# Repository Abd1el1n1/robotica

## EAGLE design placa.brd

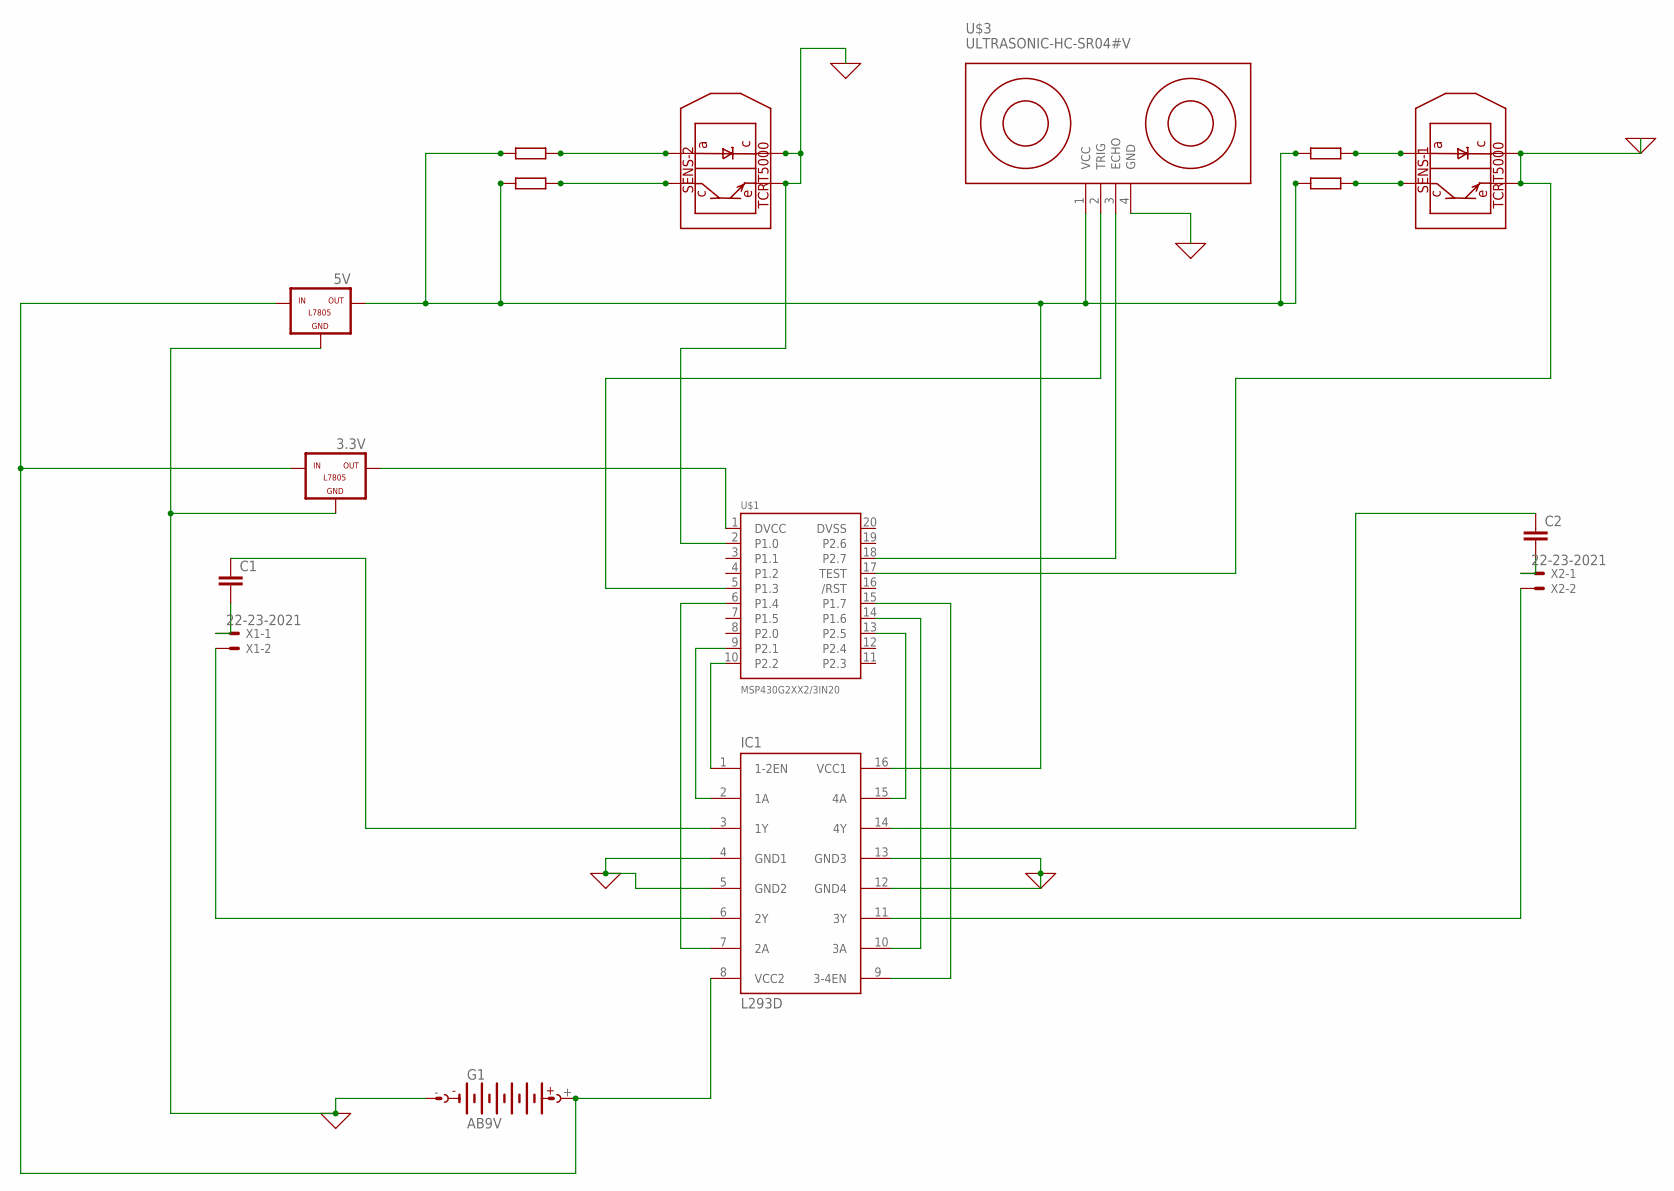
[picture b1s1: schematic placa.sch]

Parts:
3.3V, 5V: -L7805; L7805
C1, C2: C2.5/2; C2.5-2
G1: AB9V
IC1: L293D; DIL16
SENS-1, SENS-2: TCRT5000; 5000
U$1: MSP430G2XX2/3IN20; DIL20
U$3: ULTRASONIC-HC-SR04#V
X1, X2: 22-23-2021

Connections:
0: 3.3V.GND, 5V.GND, G1.-, IC1.4 (GND1), IC1.5 (GND2), IC1.12 (GND4), IC1.13 (GND3), SENS-1.P$2, SENS-1.P$4, SENS-2.P$2, SENS-2.P$4, U$1.2 (P1.0), U$1.17 (TEST), U$3.4 (GND)
DVSS: U$1.20 (DVSS)
unnamed: 3.3V.OUT, U$1.1 (DVCC)
unnamed: IC1.1 (1-2EN), U$1.10 (P2.2)
unnamed: IC1.2 (1A), U$1.9 (P2.1)
unnamed: IC1.7 (2A), U$1.6 (P1.4)
unnamed: C1.1, IC1.3 (1Y)
unnamed: C1.2, X1.1
unnamed: IC1.15 (4A), U$1.13 (P2.5)
unnamed: IC1.10 (3A), U$1.14 (P1.6)
unnamed: IC1.9 (3-4EN), U$1.15 (P1.7)
unnamed: IC1.11 (3Y), X2.2
unnamed: IC1.6 (2Y), X1.2
unnamed: C2.2, X2.1
unnamed: C2.1, IC1.14 (4Y)
unnamed: 5V.OUT, IC1.16 (VCC1), U$3.1 (VCC)
unnamed: 3.3V.IN, 5V.IN, G1.+, IC1.8 (VCC2)
unnamed: U$1.5 (P1.3), U$3.2 (TRIG)
unnamed: U$1.18 (P2.7), U$3.3 (ECHO)

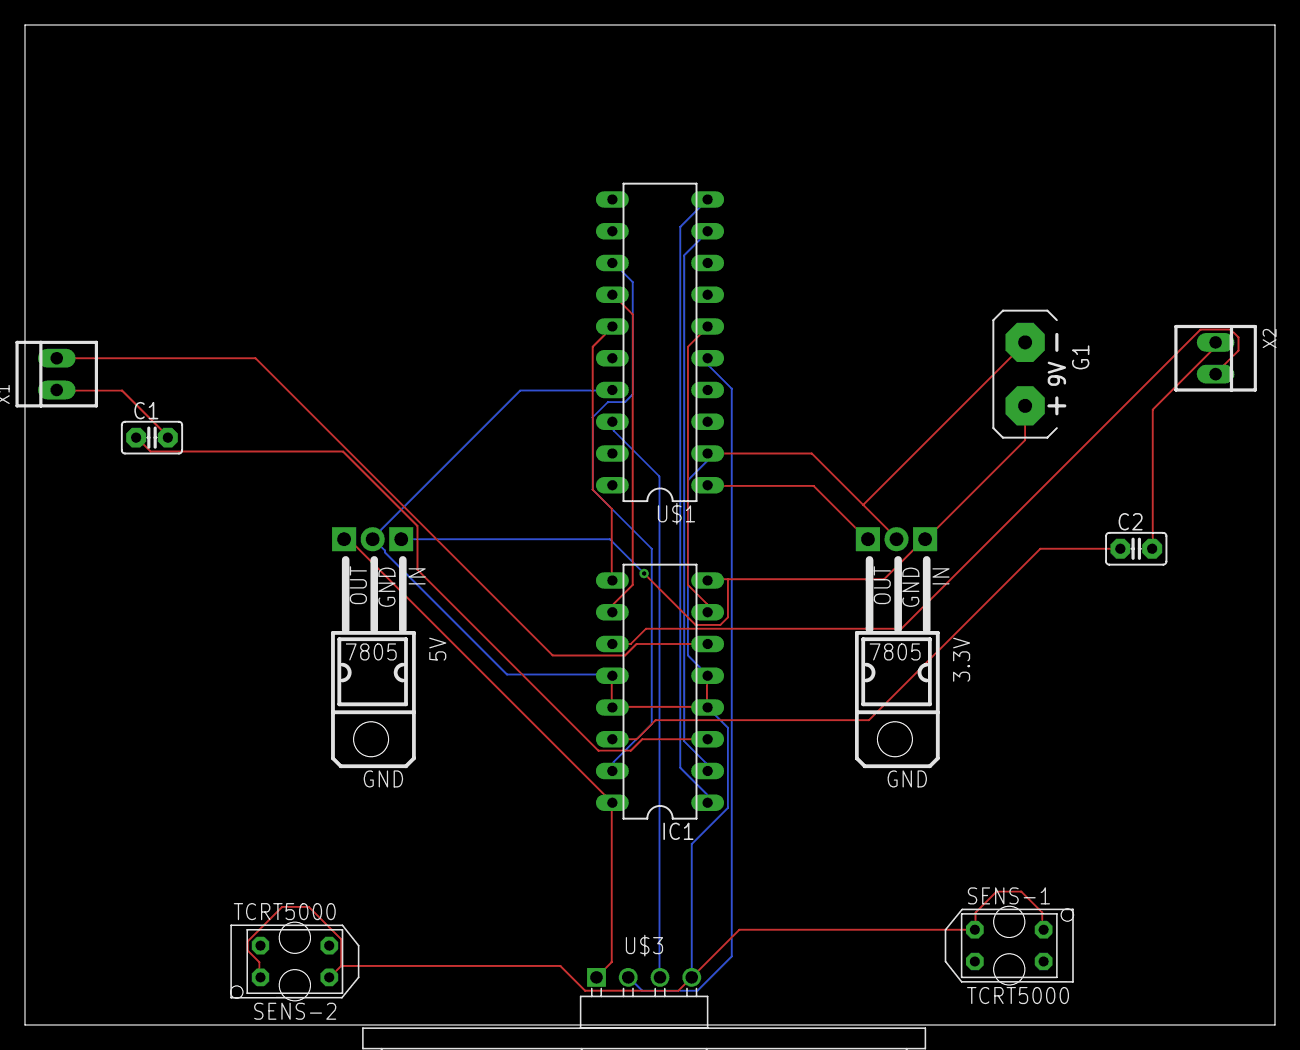
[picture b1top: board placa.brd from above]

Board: 2 copper layers, 100.0 x 80.0 mm, 12 parts (0 on the bottom side), 18 nets.

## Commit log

2020-06-05 partes del robot

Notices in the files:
parts and their libraries:
diy-modules: Released under the Creative Commons Attribution 4.0 International License: http://creativecommons.org/licenses/by/4.0
